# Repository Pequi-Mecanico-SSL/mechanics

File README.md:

# Pequi Mecânico SSL — Mechanics

Modelos de componentes e desenhos dimensionais para integração mecânica do robô SSL-EL. Seleção revisada em 26/09/2026 a partir dos nove arquivos iniciais fornecidos pela equipe, com a conversão adicional da placa de chute ZJUNlict Booster Board.

## Componentes para a montagem

Importar os modelos de `components/` no CAD do chassi. As quantidades indicadas são por robô; os arquivos não constituem uma montagem completa nem comprovam encaixes e folgas.

| Modelo | Qtd. | Utilização e conferência necessária |
| --- | ---: | --- |
| [Raspberry Pi 4 Model B](components/raspberry-pi-4-model-b.step) | 1 | Computador embarcado: suporte, acesso aos conectores e espaço para o HAT. [Desenho dimensional](references/raspberry-pi-4-model-b-dimensions.pdf). |
| [ST B-G431B-ESC1](components/st-b-g431b-esc1.step) | 4 | Controlador de cada motor: suporte, ventilação e cabos. Conferir se a placa destacável ST-LINK/BEC permanece no conjunto real. |
| [Nanotec DF45L024048-A](components/nanotec-df45l024048-a.step) | 4 | Motor de cada roda: fixação, posição e acoplamento ao cubo. |
| [GTF omniwheel 50 mm v4](components/gtf-omniwheel-50mm-v4.step) | 4 | Referência de roda omnidirecional: interferências, cubo e folga dos roletes. O projeto documenta rodas de 50 mm, mas a marca/revisão deste modelo precisa ser conferida na peça real. |
| [Pololu MinIMU-9 v5](components/pololu-minimu-9-v5.step) | 1 | Suporte da IMU: orientação dos eixos e acesso à fiação I2C. |
| [Waveshare RS485 CAN HAT](components/waveshare-rs485-can-hat.step) | 1 | Montagem sobre a Raspberry Pi: espaçadores, altura e saída dos cabos CAN. Conferir revisão da placa. |

As funções foram confrontadas com o TDP 2026 fornecido localmente e os repositórios [motor-controller](https://github.com/Pequi-Mecanico-SSL/motor-controller) e [pequi_ssl_el](https://github.com/Pequi-Mecanico-SSL/pequi_ssl_el). O [código de cinemática](https://github.com/Pequi-Mecanico-SSL/pequi_ssl_el/blob/3afe7e71667017f5217aa777948763932293336f/src/robot_control/robot_control/kinematics.py) usa raio efetivo de roda de 24,5 mm; não alterar essa calibração apenas pelo nome nominal de 50 mm do modelo.

## Placa de chute

A [referência da ZJUNlict Booster Board](references/kicker-board/README.md) inclui [STEP parcial](references/kicker-board/zjunlict-booster-board-partial.step), [STEP da placa nua](references/kicker-board/zjunlict-booster-board-bare.step), projeto editável no KiCad e prévia. Ambos os STEP passaram na validação geométrica do FreeCAD.

O contorno foi recuperado da camada mecânica e mede aproximadamente 147,71 × 129,09 mm. Apenas quatro dos 86 footprints têm modelos 3D associados. A espessura nominal importada de 0,41116 mm e os pequenos ajustes usados para fechar o contorno precisam ser conferidos na placa real; consultar as notas de conversão antes de dimensionar suportes ou folgas.

## Referências candidatas

Estes três arquivos são úteis para estudar fixações e passagem de cabos, mas sua adoção no robô ainda não está confirmada.

| Referência | Utilização e limite |
| --- | --- |
| [MR60PB-M-G-Y de 3 pinos](references/candidates/mr60pb-m-g-y-3pin.step) | Candidato para conexão das fases do motor. Conferir versão para placa, conector complementar e espaço para os cabos. |
| [XT90 macho](references/candidates/xt90-male.ipt) | Candidato para conexão de alimentação. Único modelo fornecido: Autodesk Inventor IPT; não há STEP e a geometria deste arquivo não foi validada. Para uso em outro CAD, exportar em software compatível. |
| [Solenoide SOLETEC 018](references/candidates/soletec-018-solenoid-dimensions.pdf) | Desenho mecânico na posição energizada: corpo de 33 × 22 × 15 mm e comprimento total de 59,5 ± 1,0 mm. Não informa tensão, força, resistência, curso completo ou ciclo de trabalho; não comprova equivalência ao solenoide customizado de 200 V citado no TDP. |

## Verificação

Os quatro ZIPs de origem passaram na verificação CRC de todas as entradas. Os sete STEP selecionados foram importados no FreeCAD 1.1.1 e passaram em `Shape.isValid()`, com geometria não vazia. Os dois PDFs foram renderizados e inspecionados. O IPT teve integridade da entrada ZIP conferida, mas não foi aberto no Inventor.

| Modelo STEP | Sólidos | Envelope X × Y × Z (mm) |
| --- | ---: | --- |
| Raspberry Pi 4B | 109 | 88,990 × 19,900 × 58,400 |
| ST B-G431B-ESC1 | 749 | 31,000 × 42,050 × 16,485 |
| Nanotec DF45L024048-A | 34 | 45,022 × 63,011 × 47,600 |
| GTF omniwheel 50 mm v4 | 89 | 48,459 × 49,200 × 12,601 |
| Pololu MinIMU-9 v5 | 1 | 20,320 × 12,700 × 2,216 |
| Waveshare RS485 CAN HAT | 95 | 65,022 × 30,022 × 18,500 |
| MR60PB-M-G-Y | 1 | 9,100 × 20,300 × 17,300 |

Os envelopes seguem a orientação original de cada modelo e incluem os detalhes modelados. Não equivalem necessariamente às dimensões nominais da placa. A validação geométrica não comprova correspondência com a peça real, montagem sem interferências ou desempenho elétrico.

## Seleção e nomes

Os modelos dos nove arquivos iniciais foram extraídos ou copiados sem alterar seu conteúdo; somente os nomes externos foram padronizados. A placa de chute foi convertida de Altium para KiCad/STEP, com os ajustes descritos em sua documentação. Os originais permanecem fora do repositório.

| Origem fornecida | Arquivo(s) aproveitado(s) |
| --- | --- |
| `raspberry-pi-4-model-b-1.snapshot.3.zip` | `Raspberry Pi 4 Model B.STEP` → `components/raspberry-pi-4-model-b.step`; `Raspberry Pi 4 Model B Dimensions.pdf` → `references/raspberry-pi-4-model-b-dimensions.pdf` |
| `B-G431B-ESC1.step` | `components/st-b-g431b-esc1.step` |
| `GTF Robots 50mm Wheel v4.step` | `components/gtf-omniwheel-50mm-v4.step` |
| `DF45L024048-A(1).stp` | `components/nanotec-df45l024048-a.step` |
| `solenoide 557 018.pdf` | `references/candidates/soletec-018-solenoid-dimensions.pdf`; modelo 018 identificado no desenho |
| `mr60pb-m-g-y-1.snapshot.1.zip` | `mr60pb-mgy_3pin.stp` → `references/candidates/mr60pb-m-g-y-3pin.step` |
| `xt90-male-plug-1.snapshot.2.zip` | `XT90 Male.ipt` → `references/candidates/xt90-male.ipt` |
| `minimu-9-v5-gyro-accelerometer-and-compass-lsm6ds33-and-lis3mdl-carrier.step` | `components/pololu-minimu-9-v5.step` |
| `RS485_CAN_HAT_3D_Drawing.zip` | `RS485_CAN_HAT_3D_Drawing/RS485_CAN_HAT.stp` → `components/waveshare-rs485-can-hat.step` |

Foram omitidos os ZIPs completos, imagens de apresentação, a montagem/peças SolidWorks e Parasolid da Raspberry Pi e os auxiliares `t19-3.stp`/`t19-3.prt.19` do HAT. Os STEP principais já permitem o estudo de posicionamento; os formatos omitidos permanecem nos downloads originais caso seja necessária edição nativa detalhada.

Para conferir a integridade dos arquivos selecionados, incluindo os modelos e o projeto da placa de chute, executar na raiz do repositório:

```sh
sha256sum -c SHA256SUMS
```

Os arquivos de terceiros foram fornecidos pela equipe sem URLs de origem ou licenças anexas identificadas. Nenhuma nova licença é atribuída a esses modelos.

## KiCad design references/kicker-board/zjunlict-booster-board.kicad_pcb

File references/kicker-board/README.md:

# Placa de chute — ZJUNlict Booster Board

Conversão do arquivo `Booster_Board-master.zip` fornecido pela equipe em 26/09/2026. Projeto original em Altium Designer, importado no KiCad 9.0.7 e exportado para STEP. Este é um modelo de referência mecânica **parcial**, não uma montagem completa nem um projeto de fabricação revisado.

## Arquivos

- [Modelo STEP parcial](zjunlict-booster-board-partial.step): placa e os quatro componentes que tinham modelos 3D incorporados e associados a footprints no projeto.
- [STEP da placa nua](zjunlict-booster-board-bare.step): substrato, contorno e furações exportadas.
- [Layout editável no KiCad](zjunlict-booster-board.kicad_pcb), com os modelos incorporados, e [configurações do projeto](zjunlict-booster-board.kicad_pro).
- [Prévia do KiCad](preview.png): mostra também cobre e serigrafia; os STEP finais omitem essas camadas visuais.

## O que foi recuperado

Foram importados 86 footprints. Quatro têm modelos 3D: `L2` (MSS1210-683MED), `C19` e `C20` (T523H477M016APE0707280) e `Designator1` (modelo denominado `power connector.STEP`). Os outros 82 footprints não têm modelos 3D associados na conversão. Sua presença no layout ou na serigrafia não significa que seu volume esteja representado no STEP.

Logo, a altura total calculada do STEP parcial **não é a altura máxima da placa montada**. Módulos MP1584, conectores, chave, capacitores e outros componentes visíveis nas fotos precisam de modelos e posições conferidos antes de validar interferências com o robô.

## Contorno mecânico

A forma de placa armazenada no campo de board shape do Altium é um polígono quase retangular, diferente do contorno recortado da placa fotografada. O desenho da camada `Mechanical 1` corresponde visualmente à foto da versão 2019 e foi usado para gerar o `Edge.Cuts` deste derivado.

O desenho mecânico original continha pequenos desencontros entre segmentos. Na cópia de trabalho foram removidos um segmento duplicado e um segmento de comprimento praticamente zero, unidos dois segmentos verticais sobrepostos, e ajustadas 26 extremidades de retas para fechar o contorno. O deslocamento máximo foi **0,311254 mm**, dentro da tolerância de agrupamento de 0,35 mm. Os arcos originais foram preservados. O contorno resultante contém 28 retas, 10 arcos e dois círculos de furos. O desenho `Mechanical 1` permanece no arquivo para comparação.

Isso é uma reconstrução do desenho fornecido, não uma medição da peça fabricada. Conferir contorno, posições dos furos e pequenas tolerâncias com a placa real antes de fabricar suportes. O arquivo original não foi alterado.

## Dimensões e validação

Ambos os STEP finais foram reabertos no FreeCAD 1.1.1 e passaram em `Shape.isValid()`, inclusive todos os sólidos individualmente.

| Arquivo | Sólidos | Envelope X × Y × Z (mm) |
| --- | ---: | --- |
| Placa nua | 1 | 147,70795 × 129,08513 × 0,32116 |
| Montagem parcial | 11 | 147,70795 × 129,08513 × 19,51116 |

O KiCad importou **0,41116 mm de espessura nominal de placa**. O STEP sem cobre exporta um substrato de **0,32116 mm**; a diferença vem das camadas externas omitidas pelo exportador. A espessura é incomum para este tipo de placa e precisa ser confirmada fisicamente. Ela foi preservada, sem assumir 1,6 mm. Os dados de empilhamento do Altium também contêm valores muito finos (núcleo de 12,6 mil e cobre de 1,4 mil por face).

O importador emitiu avisos `Unexpected Layer ID`; o resultado foi inspecionado para referência mecânica, não validado eletricamente ou para fabricação. A primeira exportação com cobre/serigrafia não passou na validação geométrica e não está incluída nesta pasta. Os STEP finais foram exportados sem esses elementos e passaram na validação.

## Reprodução da exportação

Na pasta deste projeto, com KiCad 9:

```sh
kicad-cli pcb export step -o booster-partial.step zjunlict-booster-board.kicad_pcb
kicad-cli pcb export step --board-only -o booster-bare.step zjunlict-booster-board.kicad_pcb
```

Na instalação Snap, substituir `kicad-cli` por `kicad.kicad-cli`. Para inspecionar, abrir o `.kicad_pcb` no PCB Editor e usar o visualizador 3D (`Alt+3`).

## Procedência

- Projeto: [ZJUNlict/Booster_Board](https://github.com/ZJUNlict/Booster_Board), versão 2019 conforme README do arquivo fornecido. As capturas 3D de 2018 também estão no ZIP e não representam a revisão 2019 completa.
- Revisão registrada no comentário do ZIP: `d5fa47cd16713b73b239209bb32c646890c3a289`.
- SHA-256 do ZIP fornecido: `a4ba0fe5ceaa91873fa818f8d310cfb279b4cea9df956c15c5282f4afe0ac4c7`.
- As fontes Altium estão no ZIP original; esta pasta contém o derivado KiCad e as exportações mecânicas. O arquivo `.kicad_pcb` incorpora os modelos 3D utilizados na exportação.

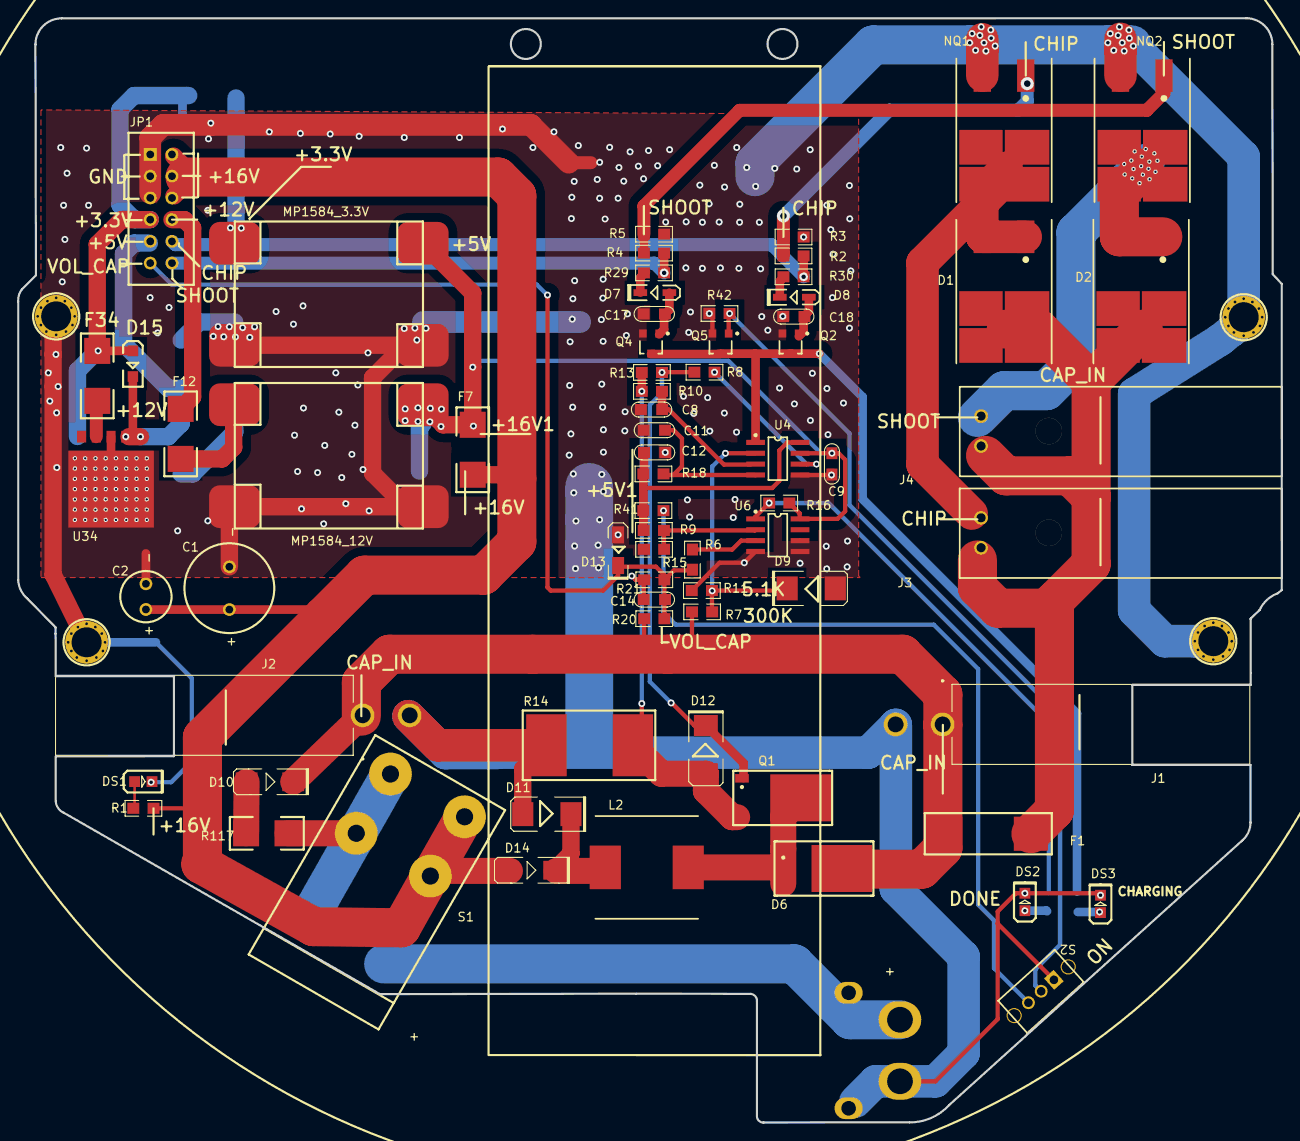
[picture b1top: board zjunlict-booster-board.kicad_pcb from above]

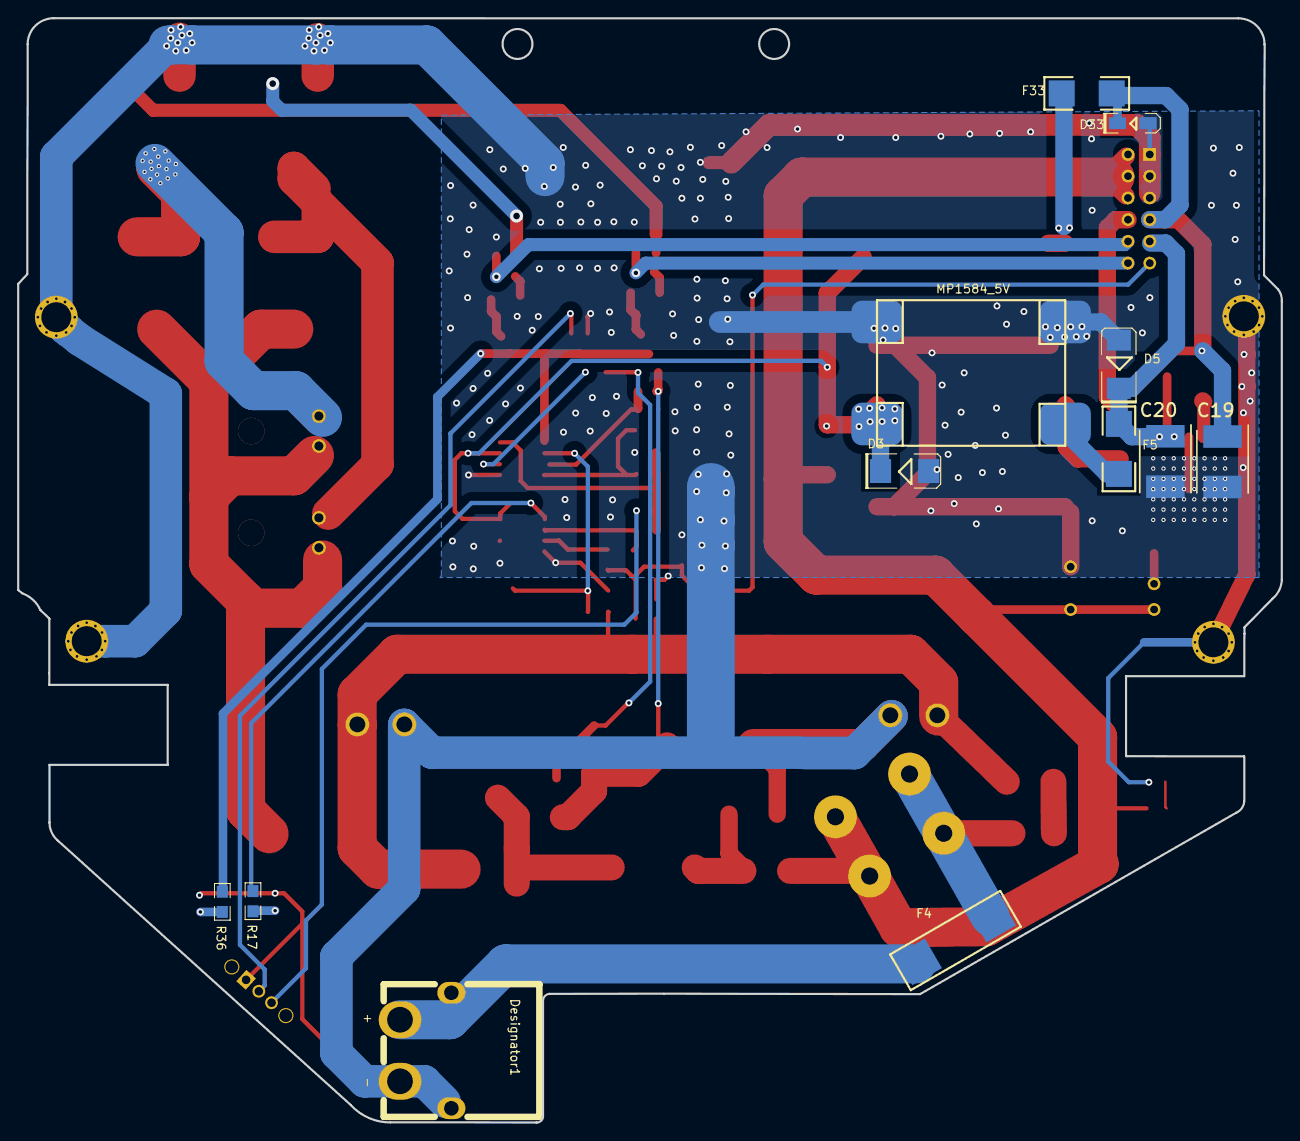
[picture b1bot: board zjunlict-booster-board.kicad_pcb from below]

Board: 2 copper layers, 147.7 x 129.1 mm, 86 parts (12 on the bottom side), 44 nets.

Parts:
C1: 330uF; 470uF
C2: 100uf; 100uF
C8: 470p; 0805C
C9, C14: 0.1uF; 0805C
C11: 2.2nf; 0805C
C12: 0.1uf; 0805C
C17, C18: 0.1uF; 0805c
C19, C20: CAP470; CAPPM7360X200N
D1, D2: MBRB40250CT; D2PAK
D3, D11, D12: SMBJ18A; SMBJ6.5
D5, D9: SMBJ6.5CA; SMBJ6.5
D6: MURD620; DPAK
D7, D8: B5819; sod-123
D10, D14: M7; SMA
D13, D33: SMF3.3; SMF33
D15: MBR120VLSFT1G SOD123; sod123
DS1, DS2: LED2; 0805A
DS3: LED3; 0805A
Designator1: Comment; XT60PW
F1, F4: 20A
F5, F7, F12, F33, F34: 3A; 2512r
J1, J2: 0768250002; 0768250002_version2
J3, J4: 172310-1102; 172310-1102_VERSION2
JP1: Header 4X2; 2*6_2.5mm
L2: 68uH; INDPM120120X1020N
MP1584_3.3V, MP1584_5V, MP1584_12V: MP1584; 1584
NQ1, NQ2: IPB64N25S3-20; D2PAK
P7, P8, P9, P10: BNC; hole
Q1: IRFR12N25D; DPAK
Q2: 9014; SOT23A
Q4: 9014; sot23a
Q5: 9014; SOT23a
R1, R3, R5, R13, R21: 10k; 0805R
R2, R4: 100; 0805r
R6, R9: 10K; 0805R
R7: 390K; 0805R
R8: 10; 0805R
R10, R15: 1k; 0805R
R11: 3.3K; 0805R
R14: 0.2; 0.2_4527R
R16, R17: 4.7k; 0805R
R18: 27k; 0805R
R20: 1m; 0805R
R29, R30: 10K; 0805r
R36: 4.7K; 0805r
R41, R42: 10k; 0805r
R117: 20; 20_2512r
S1: power; Rocker_Switch
S2: SW-SPDT; SMALL_switch
U4: UC3843P; SO-G8
U6: LM393; LM393_SO-G8
U34: BA33DD0WHFP; HRP5_16TO5

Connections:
+3.3V: C19.1, D15.1, D33.2, F33.1, F34.2, JP1.7
+5V: C20.1, D5.2, D15.2, F5.1, JP1.9, U34.1, U34.2
+5V1: C12.1, R9.2, R18.2, R41.2, U4.8
+12V: F12.1, JP1.8
+16V: C1.1, C2.1, D14.1, F7.2, JP1.2, JP1.4, JP1.6, R1.2, S1.1, S1.3
+16V1: C9.2, D3.2, F7.1, MP1584_3.3V.2, MP1584_5V.2, MP1584_12V.2, R16.2, U4.7, U6.8
BATTERY: Designator1.2, F4.2
BATTERY_IN: F4.1, R117.2, S1.2, S1.4
CHIP: JP1.10, R2.1, R30.1
CMPEN: Q2.3, Q4.3, Q5.3, R36.2, U4.1
COIL_CHIP: D1.1, D1.3, J3.2, NQ1.2
COIL_SHOOT: D2.1, D2.3, J4.2, NQ2.2
CURRENT: C8.1, R10.2, U4.3
GND: C1.2, C2.2, C8.2, C9.1, C11.2, C12.2, C14.1, C17.1, C18.1, C19.2, C20.2, D3.1, D5.1, D9.1, D11.1, D13.1, D33.1, DS1.2, DS2.2, DS3.2, Designator1.1, J1.2, J2.2, JP1.1, JP1.3, JP1.5, MP1584_3.3V.1, MP1584_3.3V.4, MP1584_5V.1, MP1584_5V.4, MP1584_12V.1, MP1584_12V.4, NQ1.3, NQ2.3, P7.1, P8.1, P9.1, P10.1, Q2.2, Q4.2, Q5.2, R3.1, R5.1, R11.1, R14.1, R15.2, R21.1, R42.2, S2.1, U4.5, U6.4, U6.5, U6.6, U34.3, U34.FIN
NetC11_1: C11.1, R18.1, U4.4
NetC17_2: C17.2, D7.1, Q4.1
NetC18_2: C18.2, D8.1, Q2.1
NetD6_1: D6.1, D6.3, L2.2, Q1.2
NetD7_2: D7.2, R29.1
NetD8_2: D8.2, R30.2
NetD10_1: D10.1, R117.1
NetD11_2: D11.2, D14.2, L2.1
NetD12_1: D12.1, Q1.3, R10.1, R13.1, R14.2
NetD12_2: D12.2, Q1.1, R8.2, R13.2
NetDS1_1: DS1.1, R1.1
NetDS2_1: DS2.1, R17.1
NetDS3_1: DS3.1, R36.1
NetF5_2: F5.2, MP1584_5V.3
NetF12_2: F12.2, MP1584_12V.3
NetF33_2: F33.2, MP1584_3.3V.3
NetF34_1: F34.1, U34.4
NetNQ1_1: NQ1.1, R2.2, R3.2
NetNQ2_1: NQ2.1, R4.2, R5.2
NetQ5_1: Q5.1, R42.1, S2.2
NetR6_1: R6.1, U6.3
NetR9_1: R9.1, R15.1, U6.2
NetR16_1: R16.1, R17.2, U6.1
NetR41_1: R41.1, S2.3
PWMOUT: R8.1, U4.6
SHOOT: JP1.12, R4.1, R29.2
VBACK: D9.2, R7.1, R11.2, U4.2
VCAP_IN: D6.2, D10.2, F1.1, J1.1, J2.1, R7.2, R20.2
VCAP_OUT: D1.2, D2.2, F1.2, J3.1, J4.1
VOLTAGE_CAP: C14.2, D13.2, JP1.11, R6.2, R20.1, R21.2
